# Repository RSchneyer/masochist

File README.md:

# masochist
the unholy offspring of a [Pain27](https://github.com/uuupah/pain27) and [Romeo](https://github.com/coseyfannitutti/romeo)

___
Thanks to Justin for the name, CFTKB for making the [Romeo](https://github.com/coseyfannitutti/romeo) (I used it as a guide), and the 40% keyboard discord server for answering my random questions

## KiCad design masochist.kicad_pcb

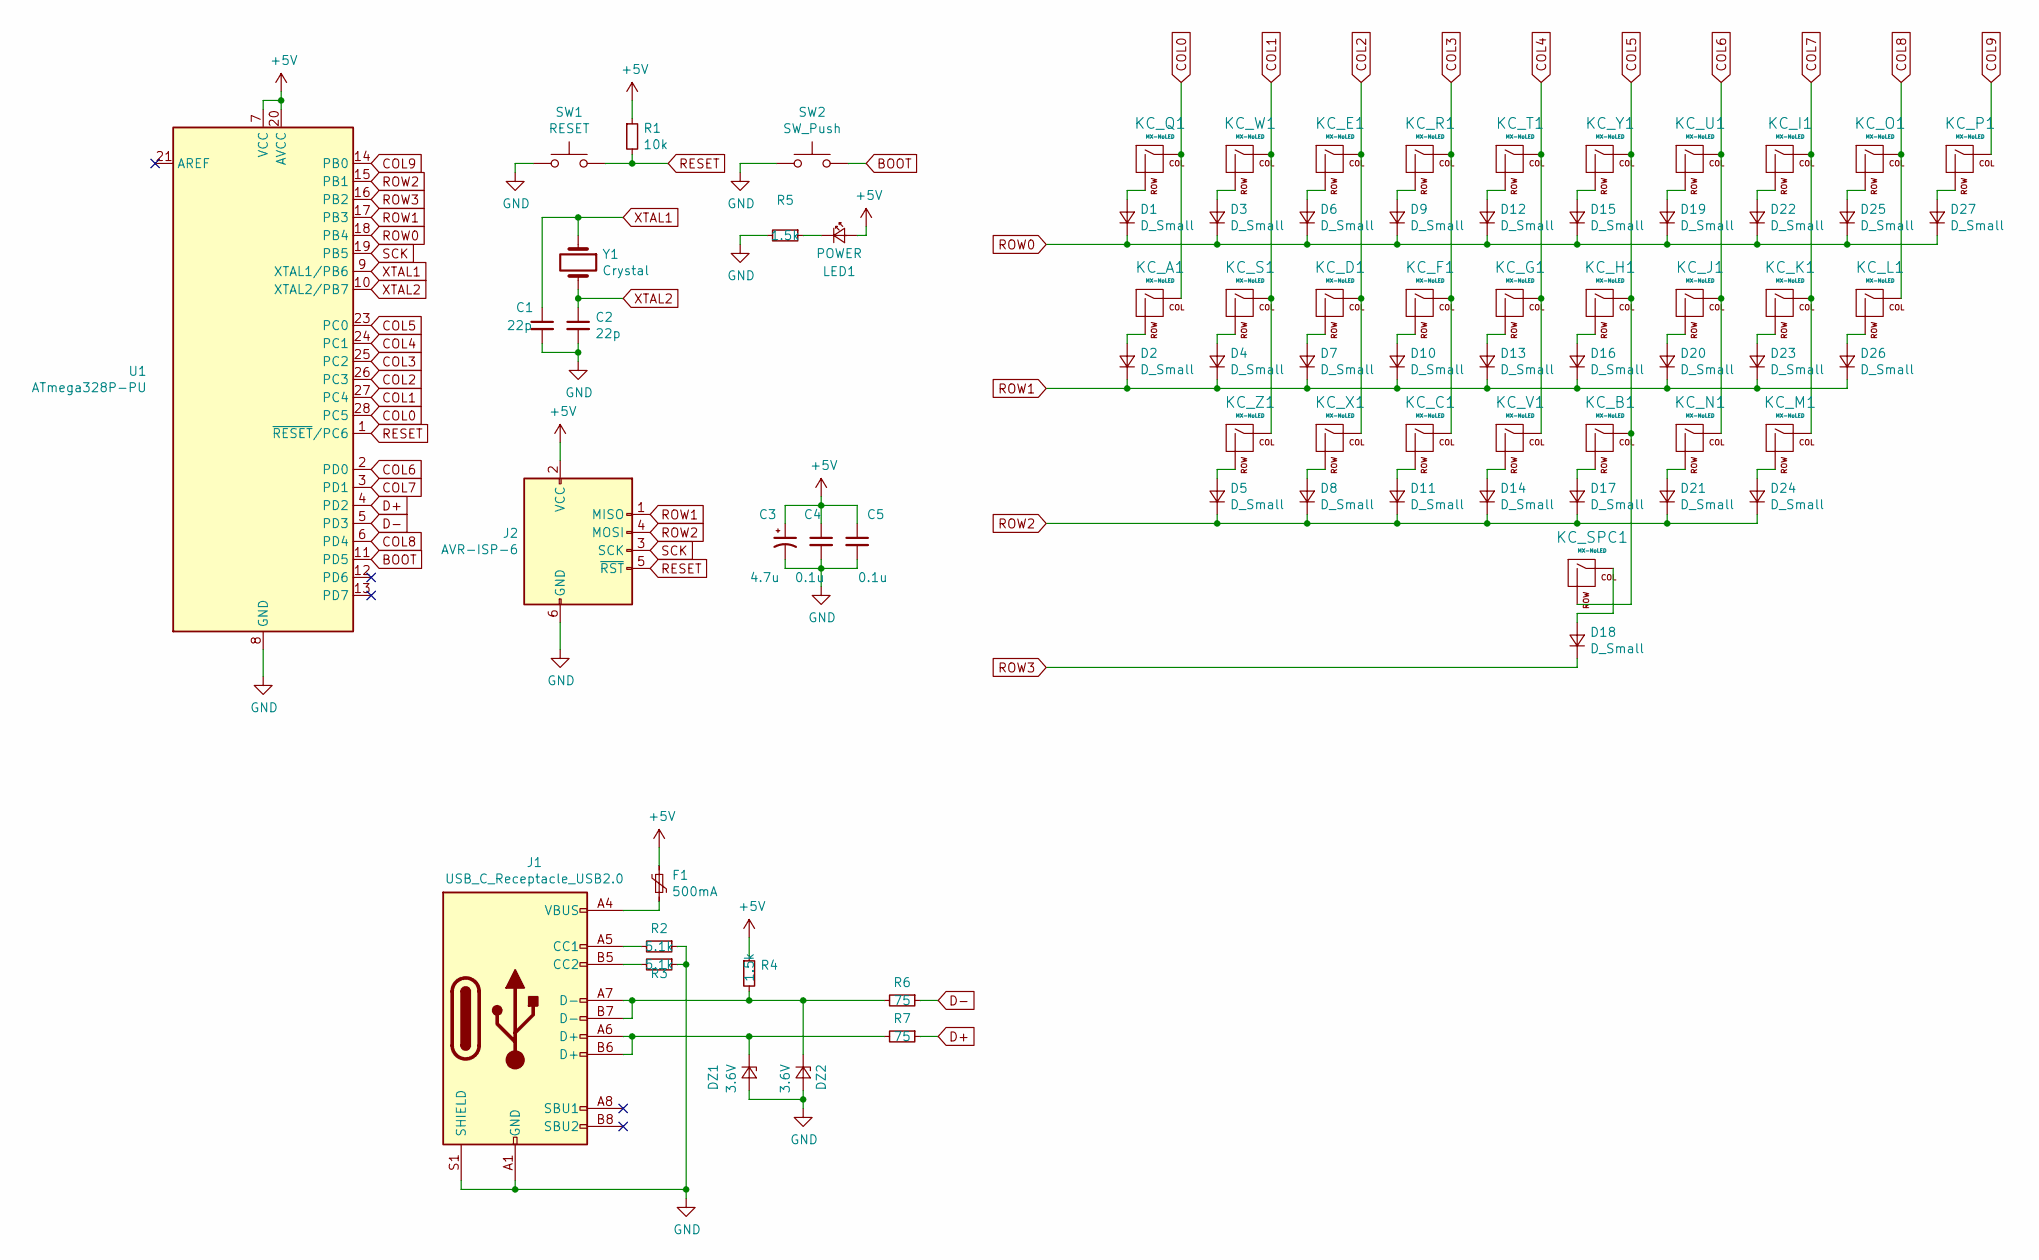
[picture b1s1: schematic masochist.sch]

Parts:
C1, C2: 22p; C_Disc_D3.0mm_W1.6mm_P2.50mm
C3: 4.7u; CP_Radial_D4.0mm_P1.50mm
C4, C5: 0.1u; C_Disc_D4.3mm_W1.9mm_P5.00mm
D1, D2, D3, D4, D5, D6, D7, D8, D9, D10, D11, D12, D13, D14, D15, D16, D17, D18, D19, D20, D21, D22, D23, D24, D25, D26, D27: D_Small; D_DO-35_SOD27_P5.08mm_Horizontal
DZ1, DZ2: 3.6V; D_DO-35_SOD27_P5.08mm_Horizontal
F1: 500mA; polyfuse_5.1mm
J1: USB_C_Receptacle_USB2.0; USB_C_GCT_USB4085
J2: AVR-ISP-6; AVR_ICSP_3x2
KC_A1: MX-NoLED; SW_Cherry_MX1A_1.00u_PCB-NOSCREEN
KC_B1: MX-NoLED; SW_Cherry_MX1A_1.00u_PCB-NOSCREEN
KC_C1: MX-NoLED; SW_Cherry_MX1A_1.00u_PCB-NOSCREEN
KC_D1: MX-NoLED; SW_Cherry_MX1A_1.00u_PCB-NOSCREEN
KC_E1: MX-NoLED; SW_Cherry_MX1A_1.00u_PCB-NOSCREEN
KC_F1: MX-NoLED; SW_Cherry_MX1A_1.00u_PCB-NOSCREEN
KC_G1: MX-NoLED; SW_Cherry_MX1A_1.00u_PCB-NOSCREEN
KC_H1: MX-NoLED; SW_Cherry_MX1A_1.00u_PCB-NOSCREEN
KC_I1: MX-NoLED; SW_Cherry_MX1A_1.00u_PCB-NOSCREEN
KC_J1: MX-NoLED; SW_Cherry_MX1A_1.00u_PCB-NOSCREEN
KC_K1: MX-NoLED; SW_Cherry_MX1A_1.00u_PCB-NOSCREEN
KC_L1: MX-NoLED; SW_Cherry_MX1A_1.00u_PCB-NOSCREEN
KC_M1: MX-NoLED; SW_Cherry_MX1A_1.00u_PCB-NOSCREEN
KC_N1: MX-NoLED; SW_Cherry_MX1A_1.00u_PCB-NOSCREEN
KC_O1: MX-NoLED; SW_Cherry_MX1A_1.00u_PCB-NOSCREEN
KC_P1: MX-NoLED; SW_Cherry_MX1A_1.00u_PCB-NOSCREEN
KC_Q1: MX-NoLED; SW_Cherry_MX1A_1.00u_PCB-NOSCREEN
KC_R1: MX-NoLED; SW_Cherry_MX1A_1.00u_PCB-NOSCREEN
KC_S1: MX-NoLED; SW_Cherry_MX1A_1.00u_PCB-NOSCREEN
KC_SPC1: MX-NoLED; MXOnly-6.25U-NoLED
KC_T1: MX-NoLED; SW_Cherry_MX1A_1.00u_PCB-NOSCREEN
KC_U1: MX-NoLED; SW_Cherry_MX1A_1.00u_PCB-NOSCREEN
KC_V1: MX-NoLED; SW_Cherry_MX1A_1.00u_PCB-NOSCREEN
KC_W1: MX-NoLED; SW_Cherry_MX1A_1.00u_PCB-NOSCREEN
KC_X1: MX-NoLED; SW_Cherry_MX1A_1.00u_PCB-NOSCREEN
KC_Y1: MX-NoLED; SW_Cherry_MX1A_1.00u_PCB-NOSCREEN
KC_Z1: MX-NoLED; SW_Cherry_MX1A_1.00u_PCB-NOSCREEN
LED1: POWER; LED_D3.0mm
R1: 10k; R_Axial_DIN0204_L3.6mm_D1.6mm_P5.08mm_Horizontal
R2, R3: 5.1k; R_Axial_DIN0204_L3.6mm_D1.6mm_P5.08mm_Horizontal
R4, R5: 1.5k; R_Axial_DIN0204_L3.6mm_D1.6mm_P5.08mm_Horizontal
R6, R7: 75; R_Axial_DIN0204_L3.6mm_D1.6mm_P5.08mm_Horizontal
SW1: RESET; SW_PUSH_6mm
SW2: SW_Push; SW_PUSH_6mm
U1: ATmega328P-PU; DIP-28_W7.62mm
Y1: Crystal; Crystal_HC49-4H_Vertical

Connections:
+5V: C3.1, C4.1, C5.1, F1.1, J2.2 (VCC), LED1.2 (A), R1.1, R4.1, U1.7 (VCC), U1.20 (AVCC)
BOOT: SW2.2, U1.11 (PD5)
COL0: KC_A1.1 (COL), KC_Q1.1 (COL), U1.28 (PC5)
COL1: KC_S1.1 (COL), KC_W1.1 (COL), KC_Z1.1 (COL), U1.27 (PC4)
COL2: KC_D1.1 (COL), KC_E1.1 (COL), KC_X1.1 (COL), U1.26 (PC3)
COL3: KC_C1.1 (COL), KC_F1.1 (COL), KC_R1.1 (COL), U1.25 (PC2)
COL4: KC_G1.1 (COL), KC_T1.1 (COL), KC_V1.1 (COL), U1.24 (PC1)
COL5: KC_B1.1 (COL), KC_H1.1 (COL), KC_SPC1.2 (ROW), KC_Y1.1 (COL), U1.23 (PC0)
COL6: KC_J1.1 (COL), KC_N1.1 (COL), KC_U1.1 (COL), U1.2 (PD0)
COL7: KC_I1.1 (COL), KC_K1.1 (COL), KC_M1.1 (COL), U1.3 (PD1)
COL8: KC_L1.1 (COL), KC_O1.1 (COL), U1.6 (PD4)
COL9: KC_P1.1 (COL), U1.14 (PB0)
D+: R7.1, U1.4 (PD2)
D-: R6.1, U1.5 (PD3)
GND: C1.2, C2.2, C3.2, C4.2, C5.2, DZ1.2 (A), DZ2.2 (A), J1.A1 (GND), J1.A12 (GND), J1.B1 (GND), J1.B12 (GND), J1.S1 (SHIELD), J2.6 (GND), R2.1, R3.1, R5.2, SW1.1, SW2.1, U1.8 (GND), U1.22 (GND)
unnamed: D1.2 (A), KC_Q1.2 (ROW)
unnamed: D2.2 (A), KC_A1.2 (ROW)
unnamed: D3.2 (A), KC_W1.2 (ROW)
unnamed: D4.2 (A), KC_S1.2 (ROW)
unnamed: D5.2 (A), KC_Z1.2 (ROW)
unnamed: D6.2 (A), KC_E1.2 (ROW)
unnamed: D7.2 (A), KC_D1.2 (ROW)
unnamed: D8.2 (A), KC_X1.2 (ROW)
unnamed: D9.2 (A), KC_R1.2 (ROW)
unnamed: D10.2 (A), KC_F1.2 (ROW)
unnamed: D11.2 (A), KC_C1.2 (ROW)
unnamed: D12.2 (A), KC_T1.2 (ROW)
unnamed: D13.2 (A), KC_G1.2 (ROW)
unnamed: D14.2 (A), KC_V1.2 (ROW)
unnamed: D15.2 (A), KC_Y1.2 (ROW)
unnamed: D16.2 (A), KC_H1.2 (ROW)
unnamed: D17.2 (A), KC_B1.2 (ROW)
unnamed: D18.2 (A), KC_SPC1.1 (COL)
unnamed: D19.2 (A), KC_U1.2 (ROW)
unnamed: D20.2 (A), KC_J1.2 (ROW)
unnamed: D21.2 (A), KC_N1.2 (ROW)
unnamed: D22.2 (A), KC_I1.2 (ROW)
unnamed: D23.2 (A), KC_K1.2 (ROW)
unnamed: D24.2 (A), KC_M1.2 (ROW)
unnamed: D25.2 (A), KC_O1.2 (ROW)
unnamed: D26.2 (A), KC_L1.2 (ROW)
unnamed: D27.2 (A), KC_P1.2 (ROW)
unnamed: DZ1.1 (K), J1.A6 (D+), J1.B6 (D+), R7.2
unnamed: DZ2.1 (K), J1.A7 (D-), J1.B7 (D-), R4.2, R6.2
unnamed: F1.2, J1.A4 (VBUS), J1.A9 (VBUS), J1.B4 (VBUS), J1.B9 (VBUS)
unnamed: J1.A5 (CC1), R2.2
unnamed: J1.B5 (CC2), R3.2
unnamed: LED1.1 (K), R5.1
RESET: J2.5 (~RST), R1.2, SW1.2, U1.1 (~RESET~/PC6)
ROW0: D1.1 (K), D3.1 (K), D6.1 (K), D9.1 (K), D12.1 (K), D15.1 (K), D19.1 (K), D22.1 (K), D25.1 (K), D27.1 (K), U1.18 (PB4)
ROW1: D2.1 (K), D4.1 (K), D7.1 (K), D10.1 (K), D13.1 (K), D16.1 (K), D20.1 (K), D23.1 (K), D26.1 (K), J2.1 (MISO), U1.17 (PB3)
ROW2: D5.1 (K), D8.1 (K), D11.1 (K), D14.1 (K), D17.1 (K), D21.1 (K), D24.1 (K), J2.4 (MOSI), U1.15 (PB1)
ROW3: D18.1 (K), U1.16 (PB2)
SCK: J2.3 (SCK), U1.19 (PB5)
XTAL1: C1.1, U1.9 (XTAL1/PB6), Y1.1
XTAL2: C2.1, U1.10 (XTAL2/PB7), Y1.2

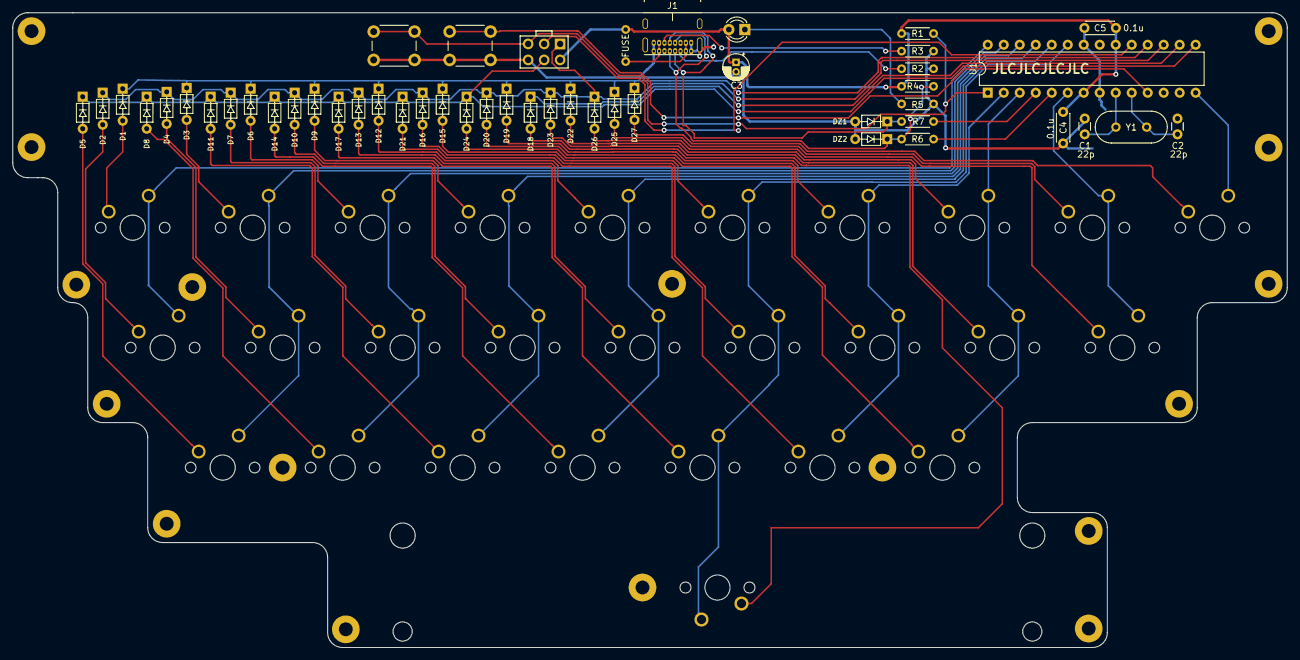
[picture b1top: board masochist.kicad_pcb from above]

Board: 2 copper layers, 202.4 x 100.8 mm, 76 parts (0 on the bottom side), 56 nets.

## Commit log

2020-05-18 added git submodules
2020-05-18 uhh started switch matrix in eeschema
2020-05-18 spelling is hard :(
2020-05-18 adding labels for stuff
    shamelessly copying how the romeo is set up
2020-05-18 more schematic stuff
2020-05-19 another commit? idk
2020-05-22 switched to USB-C 2.0 receptacle and wired it up
2020-05-22 finished schematic??
2020-05-22 added no connection flags to mcu
2020-05-23 another commit ig
2020-05-24 updated component names
2020-05-24 added cftkb.pretty folder from Romeo keyboard
2020-05-24 started adding footprints
2020-05-24 spaghetti mess of a pcb
2020-05-24 laying out the switches and diodes
2020-07-01 Project is NOT dead, components are roughly in place
2020-07-01 putting down some traces
2020-07-01 actually putting down some traces
2020-07-01 More traces (switches and matrix diodes)
2020-07-01 reassigning pins to hopefully make routing easier
2020-07-01 added PCB edges so I could see the render
2020-07-01 Updated README with render image
2020-07-01 Forgot to connect the BOOT switch to anything in the schematic
2020-07-02 updated pin assignments to make routing easier
2020-07-02 Traces Complete!
2020-07-02 Updated README with renders of front and back
2020-07-02 i dunno what i did
2020-07-02 added some mounting holes, waiting for feedback
2020-07-02 passes DRC, all traces connected
2020-07-02 added some cool dude's face to the silkscreen B)
2020-07-04 update the readme with some thanks and new renders
2020-07-04 Added a License
    forgot to do that earlier, whoops
2020-07-06 Added new logo silkscreen to PCB
2020-07-06 added logo file to silkscreens folder
2020-07-06 added renders/media folder
2020-07-06 Updated README with relative image links
2020-07-06 readme update
2020-07-10 Added GND plane to MCU and created gerbers
    im honestly just procrastinating ordering the pcbs lol
2020-07-10 Other changes? idk
2020-08-02 forgot to upload zipped gerber files, whoops
2020-08-02 updated silkscreen, regen gerbers
2020-08-28 Flipped spacebar and rerouted traces
2020-09-11 edited edge cuts so the edge is closer to the spacebar stab
2020-10-12 Updated PCB renders
2020-10-13 added more mounting holes i love mounting holes
2020-10-14 new gerbers
2020-10-14 added order number location to silkscreen
2020-11-11 regenerated & reordered gerbers
2020-11-20 Added photo of rev1 PCBs
2020-11-20 Updated README with photos
